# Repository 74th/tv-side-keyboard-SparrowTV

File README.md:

# TV Side Keyboard SparrowTV

> TV Side Keyboard SparrowTV | ProtoPedia
>
> https://protopedia.net/prototype/4340

> (530) Introduce TV Side Keyboard SparrowTV - YouTube
>
> https://www.youtube.com/watch?v=BaXQt75BodM

この作品は M5Stack Japan Creativity Contest 2023 に応募していました。

ESP32-S3 の USB デバイス機能が使いこなせなかった（USB キーボードでスリープ復帰ができないのを解決できなかった）ので、USB デバイスとして CH9329 を利用し、さらに ESP32-C3 に置き換えました。

## Product versions

### v1.2.0

- ESP32-S3 を ESP32-C3 に置き換え。
- USB キーボードのための IC として CH9329 を利用。
- キーボードマトリックス、ジョイスティックの読み込みに CH32V003F4P6 を利用（v1.0.0 ではジョイスティックのみであった）。

#### Documents

- semantics [pdf](./pcb-kicad/tv-side-keyboard_v1.2.0_semantics.pdf) [kicanvas](https://kicanvas.org/?github=https%3A%2F%2Fgithub.com%2F74th%2Ftv-side-keyboard-SparrowTV%2Fblob%2Fv1.2.0%2Fpcb-kicad%2Ftv-side-keyboard.kicad_sch)
- pcb [kicanvas](https://kicanvas.org/?github=https%3A%2F%2Fgithub.com%2F74th%2Ftv-side-keyboard-SparrowTV%2Fblob%2Fv1.2.0%2Fpcb-kicad%2Ftv-side-keyboard.kicad_pcb)

#### BOM

| Reference                    | Name                                        | Quantity |
| ---------------------------- | ------------------------------------------- | -------- |
| C1, C2                       | Capacitor 0805 10uF                         | 2        |
| C3, C4, C6, C8-C10, C12, C13 | Capacitor 0805 100nF                        | 8        |
| C5, C7, C11                  | Capacitor 0805 1uF                          | 3        |
| CH1                          | HY2.0 Socket SMD 4Pin - M5 IR Unit          | 1        |
| D1-D15                       | Diode SMD 1N4148W                           | 15       |
| D16-D30                      | RGBLED 3528 SK6812MINI-E                    | 15       |
| J1                           | USB Type-C Receptacle                       | 1        |
| J2                           | Box Pin Header 2x3 Pitch 1.27mm             | 1        |
| R1                           | Register 0805 1Ω                            | 1        |
| R2                           | Register 0805 27Ω                           | 1        |
| R3, R4, R8, R9               | Register 0805 10kΩ                          | 4        |
| R5                           | Register 0805 42-56kΩ                          | 1        |
| R6, R7                       | Register 0805 5.1kΩ                         | 2        |
| R10, R11                     | Register 0805 1kΩ                           | 2        |
| SW1-SW15                     | Kailh Choc Switch Socket                    | 15       |
| U1                           | Joystick B10K                               | 1        |
| U2                           | MCU TSSOP20 WCH CH32V003F4P6                | 1        |
| U3                           | Regulator 3.3V SOT-223 AMS1117-3.3          | 1        |
| U4                           | USB Keyboard Mouse Device IC SOIC-16 CH9329 | 1        |
| U5                           | USB Power Protection IC SOT-23-6L CH217K    | 1        |
| U6                           | WiFi MCU Module ESP32-C3-WROOM-02           | 1        |

### v1.0.0

- semantics: [PDF](pcb-kicad/tv-side-keyboard_v1.0.0_semantics.pdf) [kicanvas](https://kicanvas.org/?github=https%3A%2F%2Fgithub.com%2F74th%2Ftv-side-keyboard-SparrowTV%2Fblob%2Fv1.0.0%2Fpcb-kicad%2Ftv-side-keyboard.kicad_sch)
- pcb: [kicanvas](https://kicanvas.org/?github=https%3A%2F%2Fgithub.com%2F74th%2Ftv-side-keyboard-SparrowTV%2Fblob%2Fv1.0.0%2Fpcb-kicad%2Ftv-side-keyboard.kicad_pcb)

#### BOM

| Reference | Name                               | Quantity |
| --------- | ---------------------------------- | -------- |
| CH1       | HY2.0 Socket SMD 4Pin - JoyPoint   | 1        |
| CH2       | HY2.0 Socket SMD 4Pin - M5 IR Unit | 1        |
| D1-D12    | Diode SMD 1N4148W                  | 12       |
| D13-D24   | RGBLED 3528 SK6812MINI-E           | 12       |
| J1        | Box Pin Header 2x3 Pitch 1.27mm    | 1        |
| R1        | Capacitor 0805 27F                 | 1        |
| R2, R3    | Capacitor 0805 10kF                | 2        |
| SW1-SW12  | Kailh Choc Switch Socket           | 12       |
| U1        | MCU Module M5Stamp S3              | 1        |

## License

MIT

日本では販売しないでいただけると助かります。

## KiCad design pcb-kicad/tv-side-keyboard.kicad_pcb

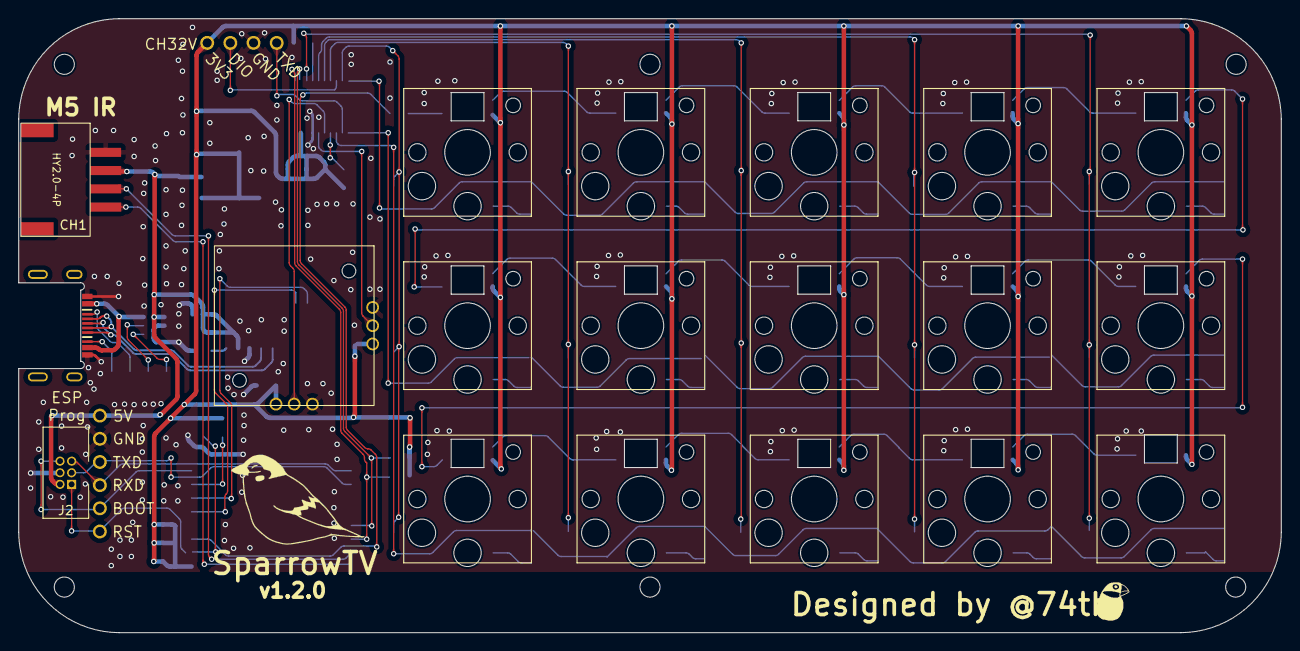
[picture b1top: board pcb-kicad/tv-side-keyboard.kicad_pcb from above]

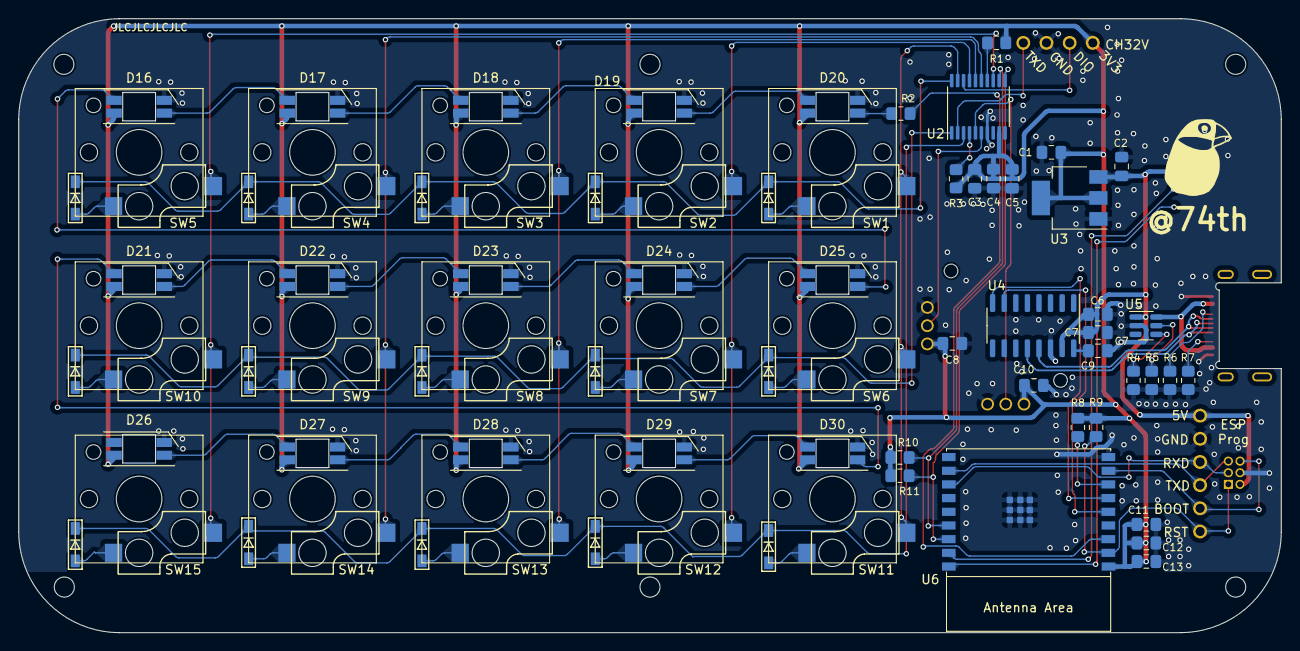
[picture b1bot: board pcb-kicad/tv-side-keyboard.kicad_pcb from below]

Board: 2 copper layers, 138.4 x 67.3 mm, 87 parts (46 on the bottom side), 67 nets.

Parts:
C1, C2: 10u; Capacitor_0805_2012
C3, C4, C6, C8, C9, C10, C12, C13: 100n; Capacitor_0805_2012
C5, C7, C11: 1u; Capacitor_0805_2012
CH1: M5 IR Unit; HY2.0_Socket_SMD_4Pin
CH2: SWD 1Wire & UART TX; PinOut_4Pin
D1, D2, D3, D4, D5, D6, D7, D8, D9, D10, D11, D12, D13, D14, D15: 1N4148W; D3_SMD_v2
D16, D17, D18, D19, D20, D21, D22, D23, D24, D25, D26, D27, D28, D29, D30: SK6812MINI; YS-SK6812MINI-E-BACK-RIGHT
J1: Keyboard USB; USB-C-12-Pin-MidMount-ali-v5
J2: ESPProg-Port; BoxPinHeader_2x03_P1.27mm_Vertical
J3: ESPProg-Port; 6Pin
M1, M2, M3, M4, M5, M6: M2-Hole
MISC-ICON: LOGO; Logo_74th_5mm
R1: 1; Register_0805_2012
R2: 27; Register_0805_2012
R3, R4, R8, R9: 10k; Register_0805_2012
R5: 42k; Register_0805_2012
R6, R7: 5.1k; Register_0805_2012
R10, R11: 1k; Register_0805_2012
SW1, SW2, SW3, SW4, SW5, SW6, SW7, SW8, SW9, SW10, SW11, SW12, SW13, SW14, SW15: SW_Push; Choc_1Side_1.0u
U1: joystick-b10k; JOYSTICK-B10K
U2: CH32V003F4P6; TSSOP-20_4.4x6.5mm_P0.65mm
U3: Regulator_AMS117-3.3; SOT-223-3_TabPin2
U4: CH9329; SOIC-16_3.9x9.9mm_P1.27mm
U5: CH217K; SOT-23-6
U6: ESP32-C3-WROOM-02

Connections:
+3.3V: C1.1, C3.1, C4.1, C5.1, C8.1, C10.1, C11.1, C12.1, C13.1, CH2.1 (VCC), D16.1 (VDD), D17.1 (VDD), D18.1 (VDD), D19.1 (VDD), D20.1 (VDD), D21.1 (VDD), D22.1 (VDD), D23.1 (VDD), D24.1 (VDD), D25.1 (VDD), D26.1 (VDD), D27.1 (VDD), D28.1 (VDD), D29.1 (VDD), D30.1 (VDD), R1.1, R3.1, R8.1, R9.1, R10.1, R11.1, U1.1 (XIN1), U1.4 (YIN1), U2.9 (VDD), U3.2 (VO), U6.1 (3V3)
+5V: C2.1, C6.1, C7.1, CH1.3 (5V), J2.2 (VCC), J3.1 (VCC), U3.3 (VI), U4.15 (VCC), U5.1 (VOUT)
/CH32V003_SWDIO: CH2.2 (SWDIO), U2.18 (SWIO/PD1)
/CH32V003_TXD: CH2.4 (TXD), U2.2 (PD5/UART_TX/ADC5)
/CH9329_DM: J1.2 (D-), U4.13 (UD-)
/CH9329_DP: J1.3 (D+), U4.12 (UD+)
/CH9329_RXD: U4.8 (RXD), U6.6 (GPIO7)
/CH9329_TXD: U4.7 (TXD), U6.5 (GPIO6)
/COL1: SW1.1, SW6.1, SW11.1, U2.19 (PD2/ADC3)
/COL2: SW2.1, SW7.1, SW12.1, U2.17 (PC7/SPI_MISO)
/COL3: SW3.1, SW8.1, SW13.1, U2.16 (PC6/SPI_MOSI)
/COL4: SW4.1, SW9.1, SW14.1, U2.15 (PC5/SPI_SCK)
/COL5: SW5.1, SW10.1, SW15.1, U2.13 (PC3)
/ESP32C3_BOOT: J2.6 (IO0), J3.5 (IO0), U6.8 (GPIO9)
/ESP32C3_RST: J2.1 (EN), J3.6 (EN), R9.2, U6.2 (EN/CHIP_PU)
/ESP32C3_RXD: J2.5 (RXD0), J3.4 (RXD0), U6.11 (GPIO20/U0RXD)
/ESP32C3_TXD: J2.3 (TXD0), J3.3 (TXD0), U6.12 (GPIO21/U0TXD)
/IR_IN: CH1.1 (IN), U6.18 (GPIO0/ADC1_CH0/XTAL_32K_P)
/IR_OUT: CH1.2 (OUT), U6.17 (GPIO1/ADC1_CH1/XTAL_32K_N)
/LED: R2.2, U6.3 (GPIO4/ADC1_CH4)
/ROW1: D1.1 (K), D2.1 (K), D3.1 (K), D4.1 (K), D5.1 (K), U2.20 (PD3/UART_CTS/ADC4)
/ROW2: D6.1 (K), D7.1 (K), D8.1 (K), D9.1 (K), D10.1 (K), U2.1 (PD4/UART_CK/ADC7)
/ROW3: D11.1 (K), D12.1 (K), D13.1 (K), D14.1 (K), D15.1 (K), U2.3 (PD6/UART_RX/ADC6)
/SCL: R10.2, U2.12 (PC2/I2C_SCL/UART_RTS), U6.15 (GPIO3/ADC1_CH3)
/SDA: R11.2, U2.11 (PC1/I2C_SDA/SPI_NSS), U6.16 (GPIO2/ADC1_CH2)
/XOUT: U1.2 (XOUT), U2.6 (PA2/ADC0/OSC_OUT)
/YOUT: U1.5 (YOUT), U2.5 (PA1/ADC1/OSC_IN)
GND: C1.2, C2.2, C3.2, C4.2, C5.2, C6.2, C7.2, C8.2, C9.2, C10.2, C11.2, C12.2, C13.2, CH1.4 (GND), CH2.3 (GND), D16.3 (GND), D17.3 (GND), D18.3 (GND), D19.3 (GND), D20.3 (GND), D21.3 (GND), D22.3 (GND), D23.3 (GND), D24.3 (GND), D25.3 (GND), D26.3 (GND), D27.3 (GND), D28.3 (GND), D29.3 (GND), D30.3 (GND), J1.4 (GND), J2.4 (GND), J3.2 (GND), R4.2, R5.2, R6.2, R7.2, U1.3 (XIN2), U1.6 (YIN2), U2.7 (VSS), U3.1 (GND), U4.14 (GND), U5.2 (GND), U6.9 (GND), U6.19 (GND)
unnamed: D1.2 (A), SW1.2
unnamed: D2.2 (A), SW2.2
unnamed: D3.2 (A), SW3.2
unnamed: D4.2 (A), SW4.2
unnamed: D5.2 (A), SW5.2
unnamed: D6.2 (A), SW6.2
unnamed: D7.2 (A), SW7.2
unnamed: D8.2 (A), SW8.2
unnamed: D9.2 (A), SW9.2
unnamed: D10.2 (A), SW10.2
unnamed: D11.2 (A), SW12.2
unnamed: D12.2 (A), SW14.2
unnamed: D13.2 (A), SW13.2
unnamed: D14.2 (A), SW15.2
unnamed: D15.2 (A), SW11.2
unnamed: D16.4 (DIN), D17.2 (DOUT)
unnamed: D16.2 (DOUT), D25.4 (DIN)
unnamed: D17.4 (DIN), D18.2 (DOUT)
unnamed: D18.4 (DIN), D19.2 (DOUT)
unnamed: D19.4 (DIN), D20.2 (DOUT)
unnamed: D20.4 (DIN), R2.1
unnamed: D21.4 (DIN), D22.2 (DOUT)
unnamed: D21.2 (DOUT), D30.4 (DIN)
unnamed: D22.4 (DIN), D23.2 (DOUT)
unnamed: D23.4 (DIN), D24.2 (DOUT)
unnamed: D24.4 (DIN), D25.2 (DOUT)
unnamed: D26.4 (DIN), D27.2 (DOUT)
unnamed: D27.4 (DIN), D28.2 (DOUT)
unnamed: D28.4 (DIN), D29.2 (DOUT)
unnamed: D29.4 (DIN), D30.2 (DOUT)
unnamed: J1.5 (CC1), R6.1
unnamed: J1.6 (CC2), R7.1
unnamed: R1.2, U2.14 (PC4/ADC2)
unnamed: R3.2, U2.4 (PD7/NRST)
unnamed: C9.1, U4.16 (V33)
unnamed: R4.1, U5.4 (EN#)
unnamed: R5.1, U5.5 (ISET)
unnamed: R8.2, U6.7 (GPIO8)
VBUS: J1.1 (VBUS), U5.6 (VIN)

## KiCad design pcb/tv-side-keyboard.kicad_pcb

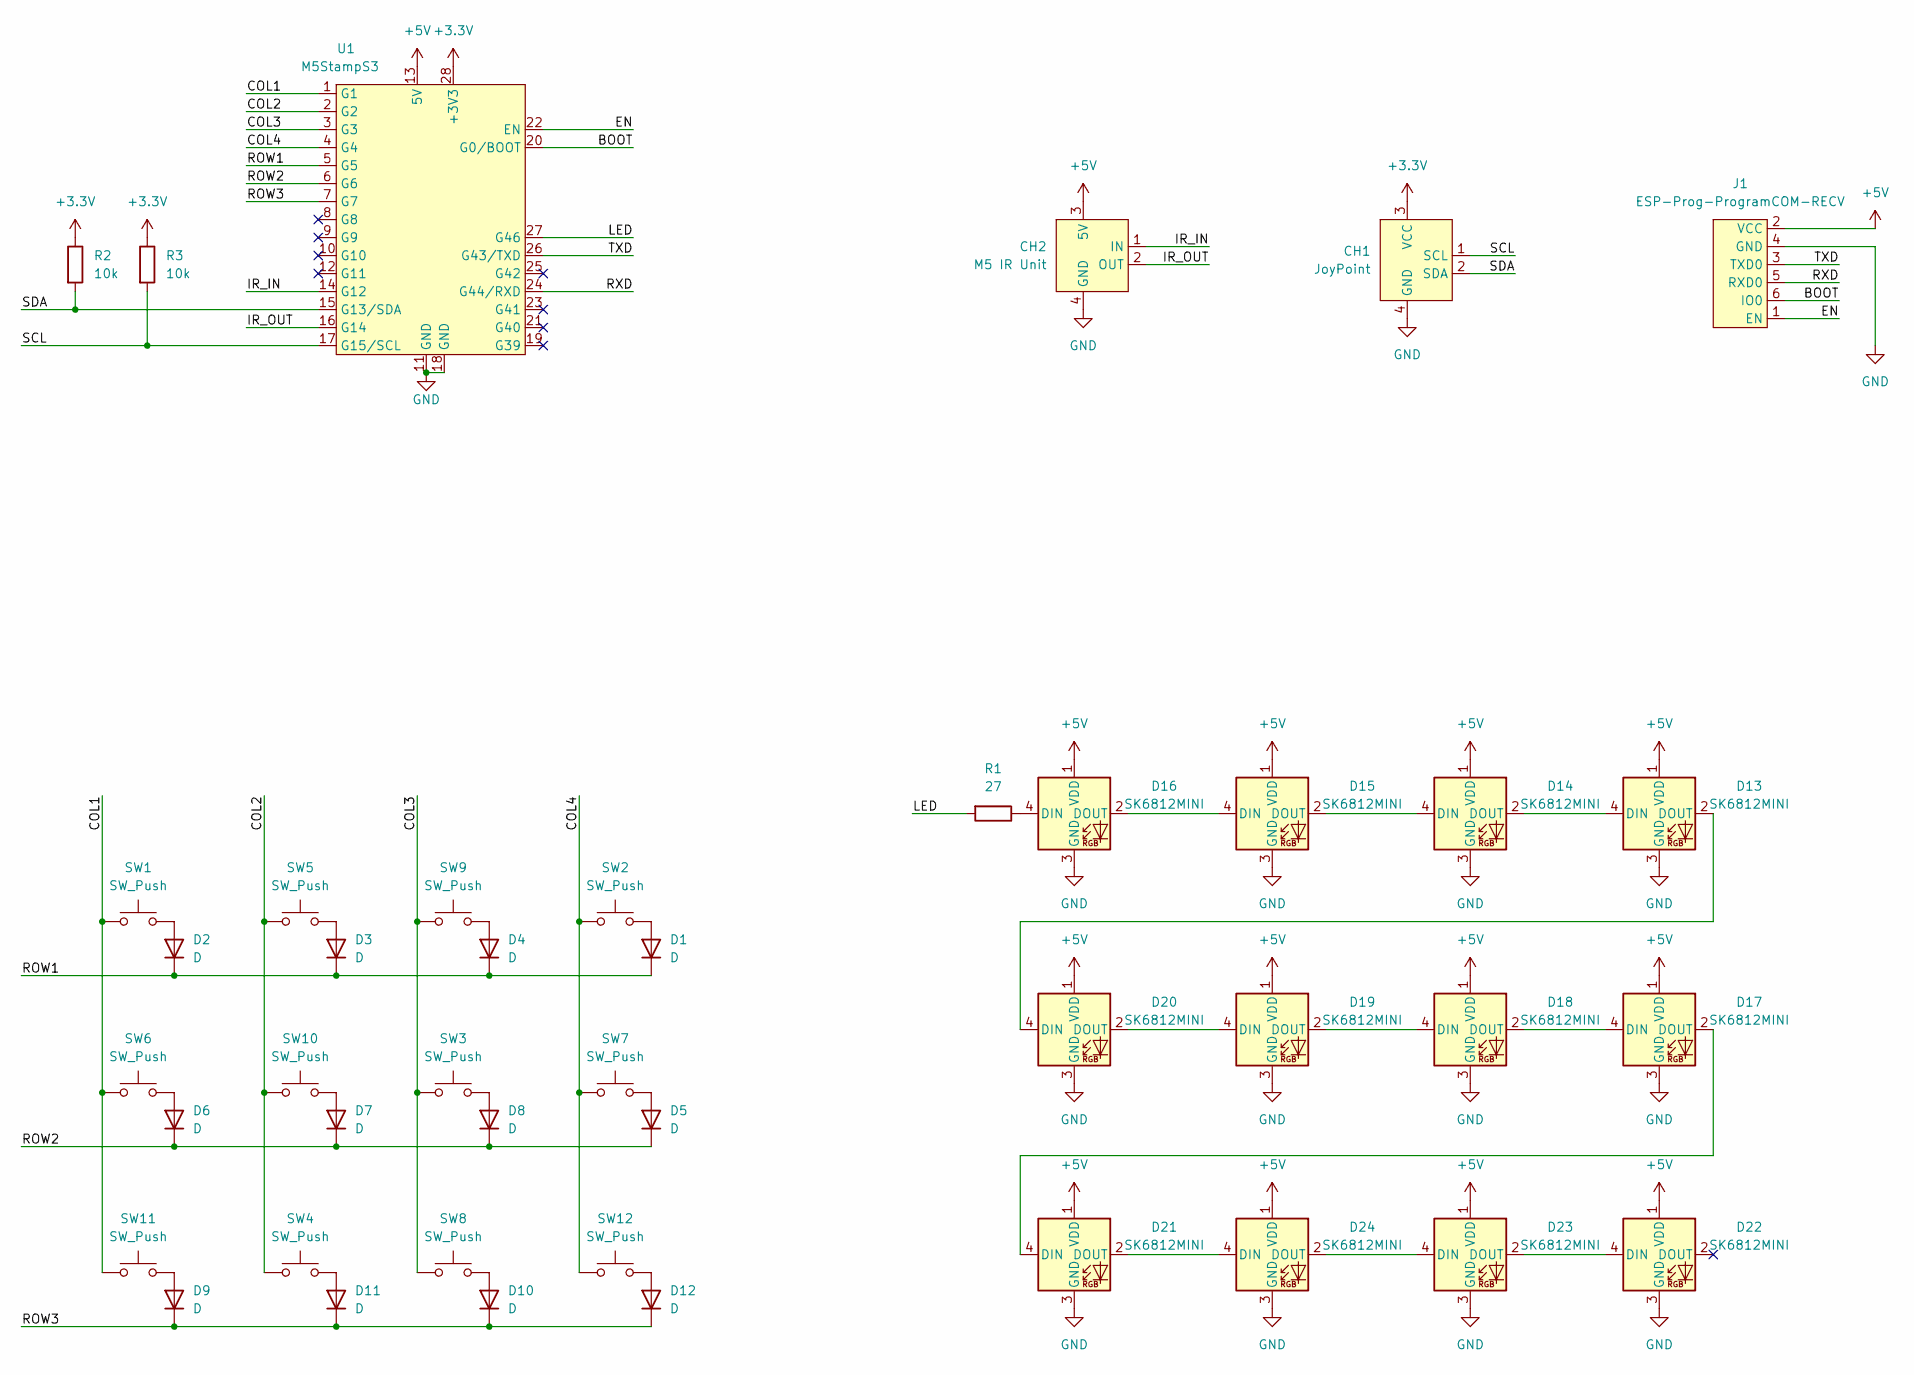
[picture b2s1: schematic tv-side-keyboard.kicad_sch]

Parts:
CH1: JoyPoint; HY2.0_Socket_SMD_4Pin
CH2: M5 IR Unit; HY2.0_Socket_SMD_4Pin
D1, D2, D3, D4, D5, D6, D7, D8, D9, D10, D11, D12: D; D3_SMD_v2
D13, D14, D15, D16, D17, D18, D19, D20, D21, D22, D23, D24: SK6812MINI; YS-SK6812MINI-E-BACK-RIGHT
J1: ESP-Prog-ProgramCOM-RECV; BoxPinHeader_2x03_P1.27mm_Vertical
R1: 27; Capacitor_0805_2012
R2, R3: 10k; Capacitor_0805_2012
SW1, SW2, SW3, SW4, SW5, SW6, SW7, SW8, SW9, SW10, SW11, SW12: SW_Push; Choc_1Side_1.0u
U1: M5StampS3; STAMP-S3-DIP

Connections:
+3V3: CH1.3 (VCC), R2.1, R3.1, U1.28 (+3V3)
+5V: CH2.3 (5V), D13.1 (VDD), D14.1 (VDD), D15.1 (VDD), D16.1 (VDD), D17.1 (VDD), D18.1 (VDD), D19.1 (VDD), D20.1 (VDD), D21.1 (VDD), D22.1 (VDD), D23.1 (VDD), D24.1 (VDD), J1.2 (VCC), U1.13 (5V)
/BOOT: J1.6 (IO0), U1.20 (G0/BOOT)
/COL1: SW1.1, SW6.1, SW11.1, U1.1 (G1)
/COL2: SW4.1, SW5.1, SW10.1, U1.2 (G2)
/COL3: SW3.1, SW8.1, SW9.1, U1.3 (G3)
/COL4: SW2.1, SW7.1, SW12.1, U1.4 (G4)
/EN: J1.1 (EN), U1.22 (EN)
/IR_IN: CH2.1 (IN), U1.14 (G12)
/IR_OUT: CH2.2 (OUT), U1.16 (G14)
/LED: R1.2, U1.27 (G46)
/ROW1: D1.1 (K), D2.1 (K), D3.1 (K), D4.1 (K), U1.5 (G5)
/ROW2: D5.1 (K), D6.1 (K), D7.1 (K), D8.1 (K), U1.6 (G6)
/ROW3: D9.1 (K), D10.1 (K), D11.1 (K), D12.1 (K), U1.7 (G7)
/RXD: J1.5 (RXD0), U1.24 (G44/RXD)
/SCL: CH1.1 (SCL), R3.2, U1.17 (G15/SCL)
/SDA: CH1.2 (SDA), R2.2, U1.15 (G13/SDA)
/TXD: J1.3 (TXD0), U1.26 (G43/TXD)
GND: CH1.4 (GND), CH2.4 (GND), D13.3 (GND), D14.3 (GND), D15.3 (GND), D16.3 (GND), D17.3 (GND), D18.3 (GND), D19.3 (GND), D20.3 (GND), D21.3 (GND), D22.3 (GND), D23.3 (GND), D24.3 (GND), J1.4 (GND), U1.11 (GND), U1.18 (GND)
unnamed: D1.2 (A), SW2.2
unnamed: D2.2 (A), SW1.2
unnamed: D3.2 (A), SW5.2
unnamed: D4.2 (A), SW9.2
unnamed: D5.2 (A), SW7.2
unnamed: D6.2 (A), SW6.2
unnamed: D7.2 (A), SW10.2
unnamed: D8.2 (A), SW3.2
unnamed: D9.2 (A), SW11.2
unnamed: D10.2 (A), SW8.2
unnamed: D11.2 (A), SW4.2
unnamed: D12.2 (A), SW12.2
unnamed: D13.4 (DIN), D14.2 (DOUT)
unnamed: D13.2 (DOUT), D20.4 (DIN)
unnamed: D14.4 (DIN), D15.2 (DOUT)
unnamed: D15.4 (DIN), D16.2 (DOUT)
unnamed: D16.4 (DIN), R1.1
unnamed: D17.4 (DIN), D18.2 (DOUT)
unnamed: D17.2 (DOUT), D21.4 (DIN)
unnamed: D18.4 (DIN), D19.2 (DOUT)
unnamed: D19.4 (DIN), D20.2 (DOUT)
unnamed: D21.2 (DOUT), D24.4 (DIN)
unnamed: D22.4 (DIN), D23.2 (DOUT)
unnamed: D23.4 (DIN), D24.2 (DOUT)

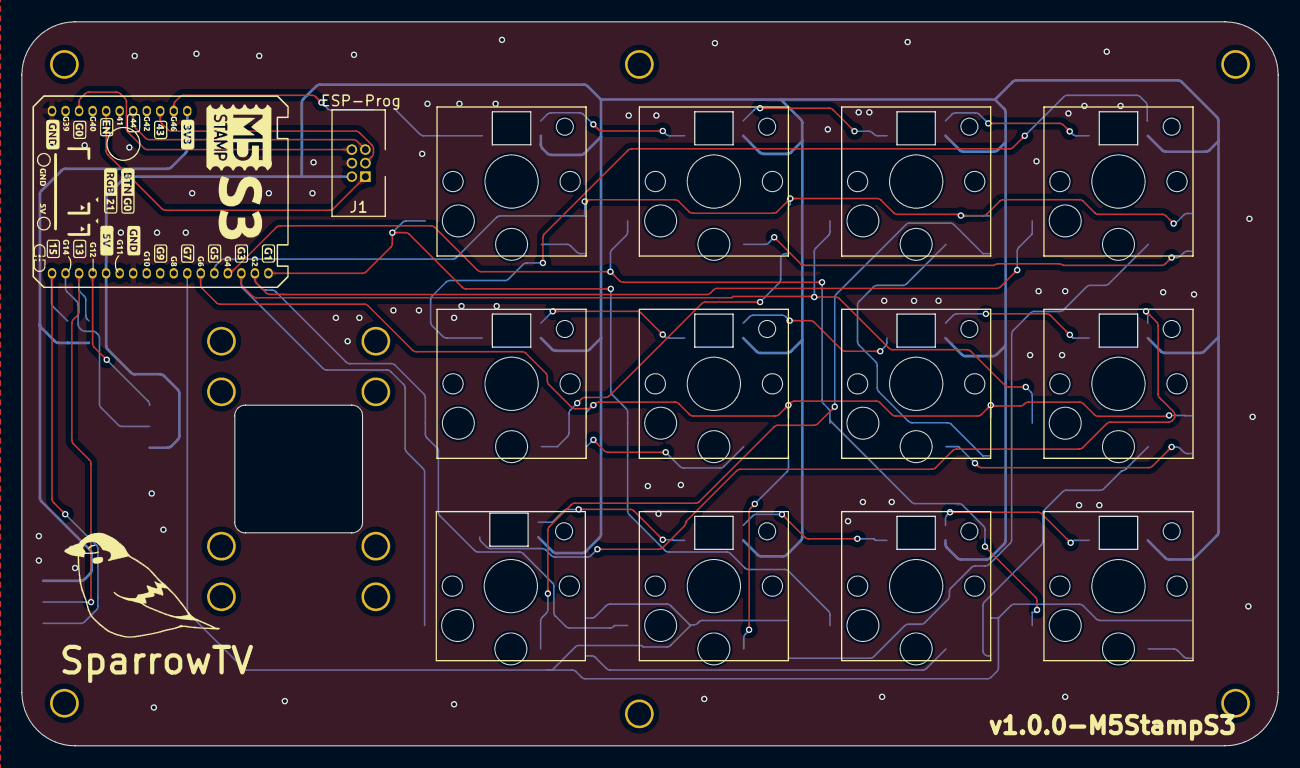
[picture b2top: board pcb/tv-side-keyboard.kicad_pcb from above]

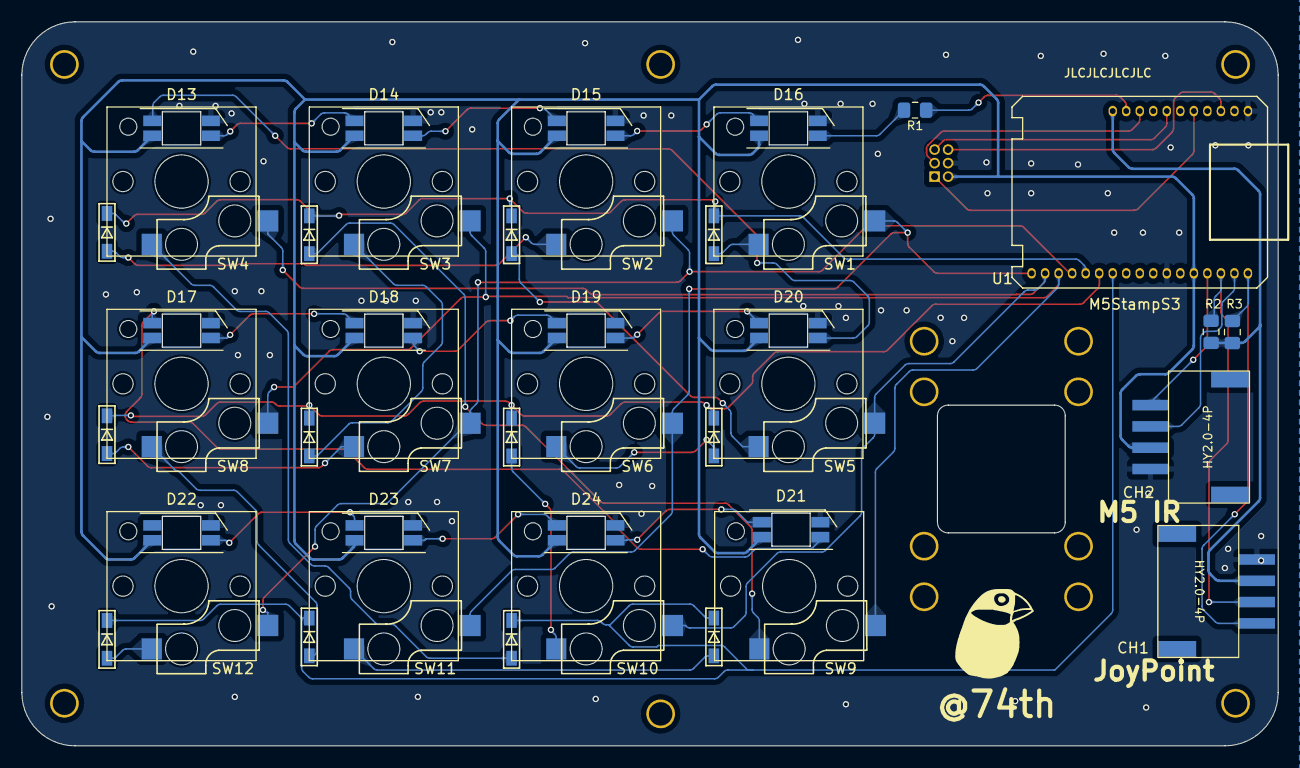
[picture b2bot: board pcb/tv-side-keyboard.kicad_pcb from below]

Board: 2 copper layers, 118.0 x 68.0 mm, 50 parts (18 on the bottom side), 43 nets.

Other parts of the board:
H1, H2, H3, H5, H6, H7: M2_v2
H4: pointer_device_top

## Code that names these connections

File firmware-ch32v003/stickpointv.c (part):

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
#define ADC_NUMCHLS 3
#define I2C_BUF_SIZE 8
#define ROW1_PIN GPIOv_from_PORT_PIN(GPIO_port_D, 3)
#define ROW2_PIN GPIOv_from_PORT_PIN(GPIO_port_D, 4)
#define ROW3_PIN GPIOv_from_PORT_PIN(GPIO_port_D, 6)
#define COL1_PIN GPIOv_from_PORT_PIN(GPIO_port_D, 2)
#define COL2_PIN GPIOv_from_PORT_PIN(GPIO_port_C, 7)
#define COL3_PIN GPIOv_from_PORT_PIN(GPIO_port_C, 6)
#define COL4_PIN GPIOv_from_PORT_PIN(GPIO_port_C, 5)
#define COL5_PIN GPIOv_from_PORT_PIN(GPIO_port_C, 3)

volatile uint8_t i2c_buf[I2C_BUF_SIZE];
volatile uint16_t adc_buf[ADC_NUMCHLS];
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{
    // https://github.com/cnlohr/ch32v003fun/blob/master/examples/i2c_slave/i2c_slave.h

    // PC1 is SDA, 10MHz Output, alt func, open-drain
    GPIOC->CFGLR &= ~(0xf << (4 * 1));
    GPIOC->CFGLR |= (GPIO_Speed_10MHz | GPIO_CNF_OUT_OD_AF) << (4 * 1);

    // PC2 is SCL, 10MHz Output, alt func, open-drain
    GPIOC->CFGLR &= ~(0xf << (4 * 2));
    GPIOC->CFGLR |= (GPIO_Speed_10MHz | GPIO_CNF_OUT_OD_AF) << (4 * 2);

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    // ADCCLK = 24 MHz => RCC_ADCPRE = 0: divide by 2
    RCC->CFGR0 &= ~(0x1F << 11);

    // A0 PA2
    GPIOA->CFGLR &= ~(0xf << (4 * 2)); // CNF = 00: Analog, MODE = 00: Input

    // A1 PA1
    GPIOA->CFGLR &= ~(0xf << (4 * 2)); // CNF = 00: Analog, MODE = 00: Input

    // A2 PA4
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{
    GPIO_port_enable(GPIO_port_C);
    GPIO_port_enable(GPIO_port_D);
    GPIO_pinMode(ROW1_PIN, GPIO_pinMode_I_pullDown, GPIO_Speed_10MHz);
    GPIO_pinMode(ROW2_PIN, GPIO_pinMode_I_pullDown, GPIO_Speed_10MHz);
    GPIO_pinMode(ROW3_PIN, GPIO_pinMode_I_pullDown, GPIO_Speed_10MHz);
    GPIO_pinMode(COL1_PIN, GPIO_pinMode_O_pushPull, GPIO_Speed_10MHz);
    GPIO_pinMode(COL2_PIN, GPIO_pinMode_O_pushPull, GPIO_Speed_10MHz);
    GPIO_pinMode(COL3_PIN, GPIO_pinMode_O_pushPull, GPIO_Speed_10MHz);
    GPIO_pinMode(COL4_PIN, GPIO_pinMode_O_pushPull, GPIO_Speed_10MHz);
    GPIO_pinMode(COL5_PIN, GPIO_pinMode_O_pushPull, GPIO_Speed_10MHz);
}

uint8_t i2c_scan_position = 0;
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        switch (col)
        {
        case 0:
            GPIO_digitalWrite_1(COL1_PIN);
            GPIO_digitalWrite_0(COL2_PIN);
            GPIO_digitalWrite_0(COL3_PIN);
            GPIO_digitalWrite_0(COL4_PIN);
            GPIO_digitalWrite_0(COL5_PIN);
            break;
        case 1:
            GPIO_digitalWrite_0(COL1_PIN);
            GPIO_digitalWrite_1(COL2_PIN);
            GPIO_digitalWrite_0(COL3_PIN);
            GPIO_digitalWrite_0(COL4_PIN);
            GPIO_digitalWrite_0(COL5_PIN);
            break;
        case 2:
            GPIO_digitalWrite_0(COL1_PIN);
            GPIO_digitalWrite_0(COL2_PIN);
            GPIO_digitalWrite_1(COL3_PIN);
            GPIO_digitalWrite_0(COL4_PIN);
            GPIO_digitalWrite_0(COL5_PIN);
            break;
        case 3:
            GPIO_digitalWrite_0(COL1_PIN);
            GPIO_digitalWrite_0(COL2_PIN);
            GPIO_digitalWrite_0(COL3_PIN);
            GPIO_digitalWrite_1(COL4_PIN);
            GPIO_digitalWrite_0(COL5_PIN);
            break;
        case 4:
            GPIO_digitalWrite_0(COL1_PIN);
            GPIO_digitalWrite_0(COL2_PIN);
            GPIO_digitalWrite_0(COL3_PIN);
            GPIO_digitalWrite_0(COL4_PIN);
            GPIO_digitalWrite_1(COL5_PIN);
            break;
        }

        Delay_Us(1);

        row1_buf |= GPIO_digitalRead(ROW1_PIN) << col;
        row2_buf |= GPIO_digitalRead(ROW2_PIN) << col;
        row3_buf |= GPIO_digitalRead(ROW3_PIN) << col;
    }
    i2c_buf[5] = row1_buf;
    i2c_buf[6] = row2_buf;
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
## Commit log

2023-07-16 add LICENSE
2023-07-17 build-pcb
2023-07-17 v1.0.0
2023-07-23 add web api
2023-07-30 add matrix buttons
2023-07-30 matrix led
2023-07-30 add pointer
2023-08-20 pcusb
2023-08-20 WIP Application
2023-08-26 master server
2023-08-28 update kicad
2023-08-29 update BOM
2023-09-09 v1.1.0
2023-09-09 add logger
2023-09-30 iphone se 2 sized
2023-09-30 v1.2.0
2023-10-21 copy from stickpoint-firmware
2023-10-21 firmware ch32v003
2023-10-21 connect ch32v003
2023-10-28 remove irremote
2023-10-28 remove rrremote
2023-10-28 add ch9329
2023-10-29 support ch9329
2025-01-26 use uv
2025-01-26 update wheel, key sequence
2025-01-26 update default config
